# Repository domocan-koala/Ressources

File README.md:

# Présentation

Ressources nécessaires pour la création d'une nouvelle carte fille [KoalaBoard](https://github.com/domocan-koala/KoalaBoard) pour le système domotique [Domocan Master Édition](https://www.abcelectronique.com/bigonoff/forum/forumdisplay.php?fid=22).

# Schéma de principe et PCB

[Projets Kicad](https://github.com/domocan-koala/Ressources/tree/master/Kicad) pour démarrer une nouvelle carte fille avec les fixations et les connecteurs 2x20 pins placés.

# Programmation

Librairies développées pour le LPC1768

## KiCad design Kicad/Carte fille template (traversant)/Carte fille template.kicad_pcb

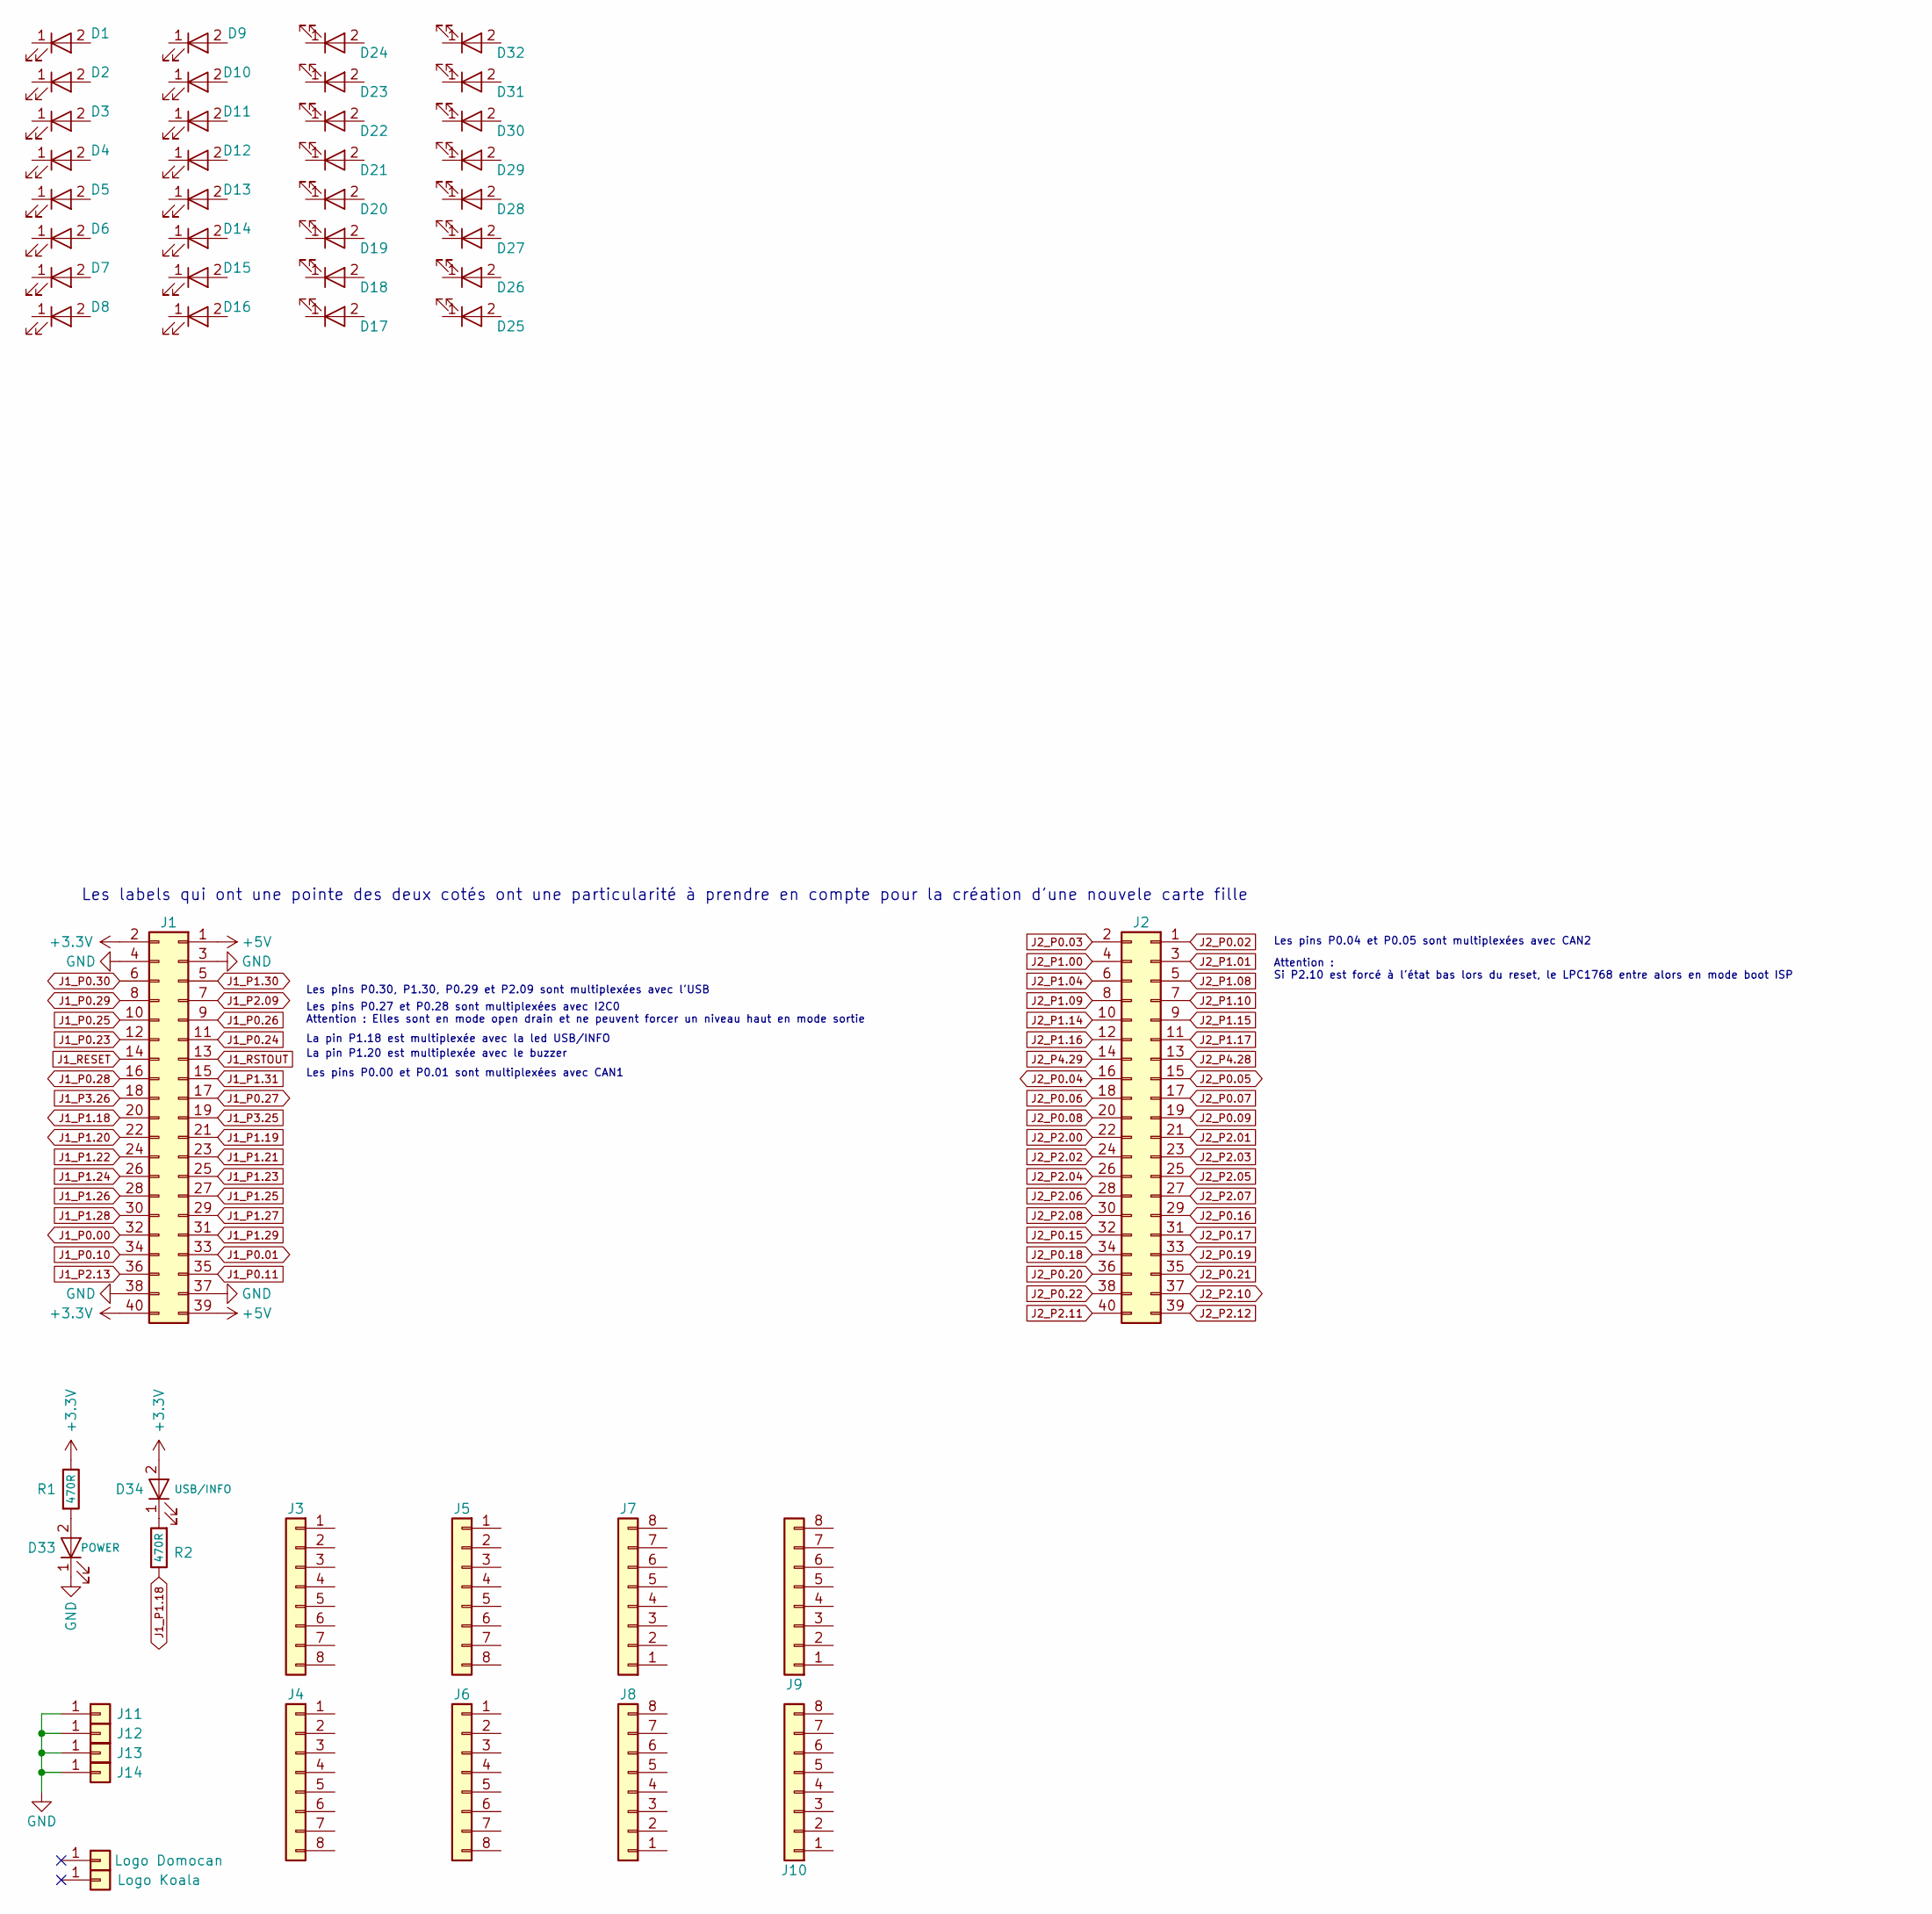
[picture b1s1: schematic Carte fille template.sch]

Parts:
D1, D2, D3, D4, D5, D6, D7, D8, D9, D10, D11, D12, D13, D14, D15, D16, D17, D18, D19, D20, D21, D22, D23, D24, D25, D26, D27, D28, D29, D30, D31, D32: LED; LED_0805_HandSoldering
D33: POWER; LED_0805_HandSoldering
D34: USB/INFO; LED_0805_HandSoldering
J1, J2: Conn_02x20_Odd_Even; Pin_Header_Straight_2x20_Pitch2.54mm
J3, J4, J5, J6, J7, J8, J9, J10: Conn_01x08; Pin_Header_Angled_1x08
J11, J12, J13, J14: Conn_01x01; MountingHole_3.5mm_Pad
J15: Logo Domocan; usb
J16: Logo Koala; koala
R1, R2: 470R; R_0805_HandSoldering

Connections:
+3V3: D34.2 (A), J1.2, J1.40, R1.1
+5V: J1.1, J1.39
GND: D33.1 (K), J1.3, J1.4, J1.37, J1.38, J11.1, J12.1, J13.1, J14.1
J1_P0.00: J1.32
J1_P0.01: J1.33
J1_P0.10: J1.34
J1_P0.11: J1.35
J1_P0.23: J1.12
J1_P0.24: J1.11
J1_P0.25: J1.10
J1_P0.26: J1.9
J1_P0.27: J1.17
J1_P0.28: J1.16
J1_P0.29: J1.8
J1_P0.30: J1.6
J1_P1.18: J1.20, R2.1
J1_P1.19: J1.21
J1_P1.20: J1.22
J1_P1.21: J1.23
J1_P1.22: J1.24
J1_P1.23: J1.25
J1_P1.24: J1.26
J1_P1.25: J1.27
J1_P1.26: J1.28
J1_P1.27: J1.29
J1_P1.28: J1.30
J1_P1.29: J1.31
J1_P1.30: J1.5
J1_P1.31: J1.15
J1_P2.09: J1.7
J1_P2.13: J1.36
J1_P3.25: J1.19
J1_P3.26: J1.18
J1_RESET: J1.14
J1_RSTOUT: J1.13
J2_P0.02: J2.1
J2_P0.03: J2.2
J2_P0.04: J2.16
J2_P0.05: J2.15
J2_P0.06: J2.18
J2_P0.07: J2.17
J2_P0.08: J2.20
J2_P0.09: J2.19
J2_P0.15: J2.32
J2_P0.16: J2.29
J2_P0.17: J2.31
J2_P0.18: J2.34
J2_P0.19: J2.33
J2_P0.20: J2.36
J2_P0.21: J2.35
J2_P0.22: J2.38
J2_P1.00: J2.4
J2_P1.01: J2.3
J2_P1.04: J2.6
J2_P1.08: J2.5
J2_P1.09: J2.8
J2_P1.10: J2.7
J2_P1.14: J2.10
J2_P1.15: J2.9
J2_P1.16: J2.12
J2_P1.17: J2.11
J2_P2.00: J2.22
J2_P2.01: J2.21
J2_P2.02: J2.24
J2_P2.03: J2.23
J2_P2.04: J2.26
J2_P2.05: J2.25
J2_P2.06: J2.28
J2_P2.07: J2.27
J2_P2.08: J2.30
J2_P2.10: J2.37
J2_P2.11: J2.40
J2_P2.12: J2.39
J2_P4.28: J2.13
J2_P4.29: J2.14
unnamed: D33.2 (A), R1.2
unnamed: D34.1 (K), R2.2

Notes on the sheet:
Attention : Si P2.10 est forcé à l'état bas lors du reset, le LPC1768 entre alors en mode boot ISP
Les pins P0.30, P1.30, P0.29 et P2.09 sont multiplexées avec l'USB
Les pins P0.27 et P0.28 sont multiplexées avec I2C0 Attention : Elles sont en mode open drain et ne peuvent forcer un niveau haut en mode sortie
La pin P1.18 est multiplexée avec la led USB/INFO
La pin P1.20 est multiplexée avec le buzzer
Les pins P0.00 et P0.01 sont multiplexées avec CAN1
Les pins P0.04 et P0.05 sont multiplexées avec CAN2
Les labels qui ont une pointe des deux cotés ont une particularité à prendre en compte pour la création d'une nouvele carte fille

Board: 2 copper layers, 52 parts (12 on the bottom side), 6 nets, no tracks yet.

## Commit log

2018-03-02 Première mise en ligne
2018-03-02 LPC1768 : Timings
    Ajout de la librairie Timing (par Bigonoff)
2018-03-03 ReadMe
    Premier test
2018-03-03 LPC1768 : Timing
    Correction nom du dossier
2018-03-03 LPC1768 : Librairies : Eeprom
    Première mise en ligne
2018-03-03 LPC1768 : Librairies : Eeprom
    Bug
2018-03-03 LPC1768 : Librairie : Eeprom
    Organisation des exemples
2018-03-03 LPC1768 : Librairie : Organisation
    Organisation des exemples
2018-03-04 LPC1768 : Librairies : CAN
    Ajout de la librairie CAN
